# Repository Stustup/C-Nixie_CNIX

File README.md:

# CNIX - Nixie Tube Clock

CNIX is a nixie tube clock that can accept many diffrent nixie tubes with only slight modifications to the tube carrier board. 

The motivation was that there are not many clocks out there that let you use almost any nixie tube you like. Most have fixed power supplies, 
underdesigned driver stages or inflexible microcontrollers. I hope to tackle these problems with an adjustable boost converter PSU, extremely 
flexible (and electrically protected) driver stages and an open source firmware written with free tools.

## **Schematic**

The control board consists of 3 parts:
- Power Supply
- Microcontroller
- I/O
- GPIO header

Power comes from a simple USB-C plug configured for 5V 3A max with the 5k1 CC line resistors. I thought about adding a PD controller for higher input voltages, but this would just have added complexity and locked you into more expensive USB PD power supplies.

The µC is a STM32G051, because it has an included RTC *with* added Vbat pin for an external battery, so that the RTC remembers time even when powered off. 
The unused GPIOs are broken out to a connector, so that in the future one could add cool stuff like a radio time reciever, a display or wifi.
Time is set manually with the push buttons on top. 

The PSU is heavily inspired by [this site](https://surfncircuits.com/2018/02/03/optimizing-the-5v-to-170v-nixie-tube-power-supply-design-part-2/). I highly advise you giving it a read. The article goes in depth with boost converter design and its challanges.

The ht power supply is a DCM boost converter powered by the UCC3803. An active low enable pin is realized via pulling the frequency RC combination low. With normal usage temperature of around 50-60°C are reached by the output transistor and the controller, which is a safe area. The case is designed so that a convection current of air is directed over the power supply at all times. This vent should not be blocked.  

The driver consists of 4 CD4028 BCD to Decimal converters and 6 SN75468 high voltage drivers. The SN75468 only work up top 100V, but when using two 48V zener diodes as clamps, the voltage on the torned off digits never reach above 100V and above the startup voltage of the nixies. So win win.

I didn't use the old high voltage nixie driving shift registers as they are more and more hard to find for a reasonable price. Also i did not use shift registers at all, to simplify programming and wiring. Instead the whole Port B of the STM32 is used as a big 16 bit control register where the numbers are encoded in BCD. This ensures that there can not be 2 turned on digits at the same time in one tube to prevent bugs and damaging the beautiful nixies. 
Except the decoupling capacitors, diopdes and LEDS, everything is a simple to reflow solder IC, The tube pins have to be assembled manually (by putting them on a tube an inserting it into the holes before soldering it to ensure perfect alignment).  

The case is designed in FreeCAD and printed in PLA or PETG. Assembly is a bit of a hassle, but the fit is perfect. You can print a front plate, but i think the clock is vastly more beautiful when paired with a wooden front plate. Drill files for this are within the CAD folder. The holes for the LED front indicators can be filled with a 3mm lightpipe cut to length, to get a beautiful finish. 
Case, PCB and front plate are screwed together with 15mm M3 wood screws.

## **Neat features**

### <u>Adaptability</u>
If you want to use any other nixie (up to around 5mA per tube of HT supply current) just modify the tube board PCB to fit your tubes. The driver, power supply and control logic should all be compatible with any other tube. Of course you have to modify the driving circuit when not using the simple common anode topology.

### <u>USB-C support</u>
Use any USB power supply with a minimum current of 1.7A (The startup of the boost converter needs a lot of current) Standard power consumption is around 2W (400mA at 5V) when the boost converter is powered on and around 0.2W (40mA at 5V) when the boost converter is powered down. 

### <u>Fallback structure</u>
If for some reason you change your mind while setting the start/stop times or the main time, just wait for around a minute. The menu will exit automatically, discard all changes and get back to the main time display.

### <u>Date and Sensor display</u>
Press the "plus" or "minus" buttons to cycle through submenus in this order: 
Main Time display -> Date display -> Sensor Display
These have a short timeout time to get back to the main Time menu. The sensor display gets disabled when there is no sensor addon board present.

### <u>Automatic daylight saving time (DST)</u>
The clock will calculate DST on its own and set the time correspondingly, even when the DCF77 module is not used.

### <u>Turn on/off timers</u>
You can set power on and off times in the clock natively, so that the nixies dont always glow. With this the HT-power supply also gets deactivated to save power and lifespan of the parts. 
There are two sets of start and stop times set by the buttons on the menu with the lower LED blinking.
The order is: Start1 -> Stop1 -> Start2 -> Stop2.
If all are set to 0, the start stop automatic gets disabled.
The start stop times are saved to a backup register of the µC, so the clock remembers them even when powered off as long as the RTC battery is present. 

#### Peek
When out of the "on" timeframes you can "peek" at the current time for 10s with a press of the menu-button. During these 10s you can jump to all the diffrent menus.

### <u>Addon Boards</u>
The breakout pins next to the µC can be used for addon boards. Pins D2 and D3 of the µC are used to detect those with an ID system. 
| ID    | Board                                 |
|-------|---------------------------------------|
| 0b11  | No Addon board installed -> defualt   |
| 0b00  | DCF77 Addon Board used                |
| 0b01  | not yet used                          |
| 0b10  | not yet used                          |

Most of the hardware features of the STM32G051 should be mapped to the pins on the breakout. If not you're out of luck (it's open source, so just change it). Stuff like the ST-Link programming pins or I2C are broken out on extra headers to simplify future expansion.

#### DCF77 Addon Board

In germany (and most of europe) we have the DCF77 signal pushed out by the radio transmitter near Frankfurt. 
This board hosts a cheap module from ebay and a HTU21D temperature and humidity sensor. The driver is already programmed into the Control Board and gets enabled when this addon board is detected. 
When a valid time is recieved the manual timeSet menu gets disabled, to prevent fuckery.
It is setup, that every night at 2 an alarm gets triggered by the RTC to recalibrate time. If the  time-parity bit is not matched within a 20 minute timeout an attempt counter is incremented, which gets saved to a backup-register inside the RTC. As long as a RTC battery is powering the µC this register is kept even when the power is off. 
If the attempt counter reches 3 days without successful calibration against the radio time the manual timeSet menu gets enabled again.

On the DCF77 Addon board there is a single pin to give structural strength to a simple perfboard on the main breakout bus. One can use this in tandem with the A1, A2, A3, A4, F0 and F1 pins.

Ideas for future addon Boards: 
- ESP32 addon board to integrate WiFi time synchronisation or HomeAssistant integration
- Other sensors like air quality sensors
- maybe displays?

## TODO

- Change to new MCU. STM32H5 for USBC pd -> more efficient boost converter because higher input voltage
- Sleep modes during off times paired with wakeup alarms at start times -> reduce power consumption even more
- Improve the case to simplify assembly
- More tube boards to fit more types of nixies (IN-14 e.G.)
- BOM optimization to reduce number of unique parts
- galvanic isolation between high voltage areas and µC GPIOs

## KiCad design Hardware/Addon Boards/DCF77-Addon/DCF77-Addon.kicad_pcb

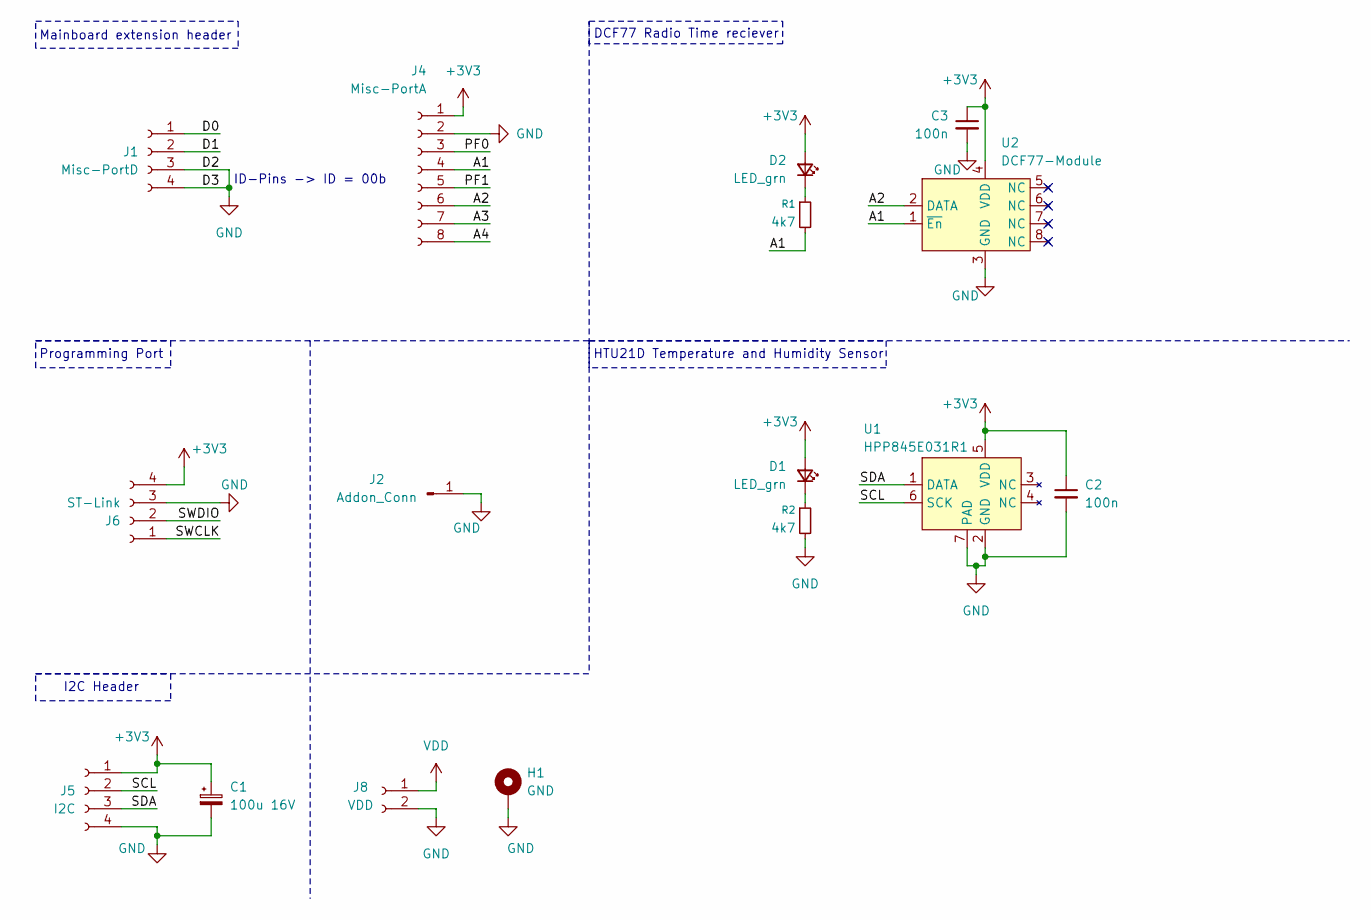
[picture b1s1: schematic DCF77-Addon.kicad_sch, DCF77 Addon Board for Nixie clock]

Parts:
C1: 100u 16V; CP_Elec_6.3x7.7
C2, C3: 100n; C_0805_2012Metric_Pad1.18x1.45mm_HandSolder
D1, D2: LED_grn; LED_0805_2012Metric_Pad1.15x1.40mm_HandSolder
H1: GND; TestPoint_Loop_D3.80mm_Drill2.0mm
J1: Misc-PortD; PinSocket_1x04_P2.54mm_Vertical
J2: Addon_Conn; PinHeader_1x01_P2.54mm_Vertical
J4: Misc-PortA; PinSocket_1x08_P2.54mm_Vertical
J5: I2C; PinSocket_1x04_P2.54mm_Vertical
J6: ST-Link; PinSocket_1x04_P2.54mm_Vertical
J8: VDD; PinSocket_1x02_P2.54mm_Vertical
R1, R2: 4k7; R_0805_2012Metric_Pad1.20x1.40mm_HandSolder
U1: HPP845E031R1; Maxim_TDFN-6-1EP_3x3mm_P0.95mm_EP1.5x2.3mm; Mouser Nr. 824-HPP845E031R1
U2: DCF77-Module

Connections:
+3V3: C1.1, C2.1, C3.1, D1.2 (A), D2.2 (A), J4.1, J5.1, J6.4, U1.5 (VDD), U2.4 (VDD)
/A1: J4.4, R1.2, U2.1 (~En)
/A2: J4.6, U2.2 (DATA)
/A3: J4.7
/A4: J4.8
/D0: J1.1
/D1: J1.2
/PF0: J4.3
/PF1: J4.5
/SCL: J5.2, U1.6 (SCK)
/SDA: J5.3, U1.1 (DATA)
/SWCLK: J6.1
/SWDIO: J6.2
GND: C1.2, C2.2, C3.2, H1.1 (1_1), J1.3, J1.4, J2.1 (Pin_1_1), J4.2, J5.4, J6.3, J8.2, R2.2, U1.2 (GND), U1.7 (PAD), U2.3 (GND)
unnamed: D1.1 (K), R2.1
unnamed: D2.1 (K), R1.1
VDD: J8.1

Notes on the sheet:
HTU21D Temperature and Humidity Sensor
DCF77 Radio Time reciever
Programming Port
ID-Pins -> ID = 00b
Mainboard extension header
I2C Header

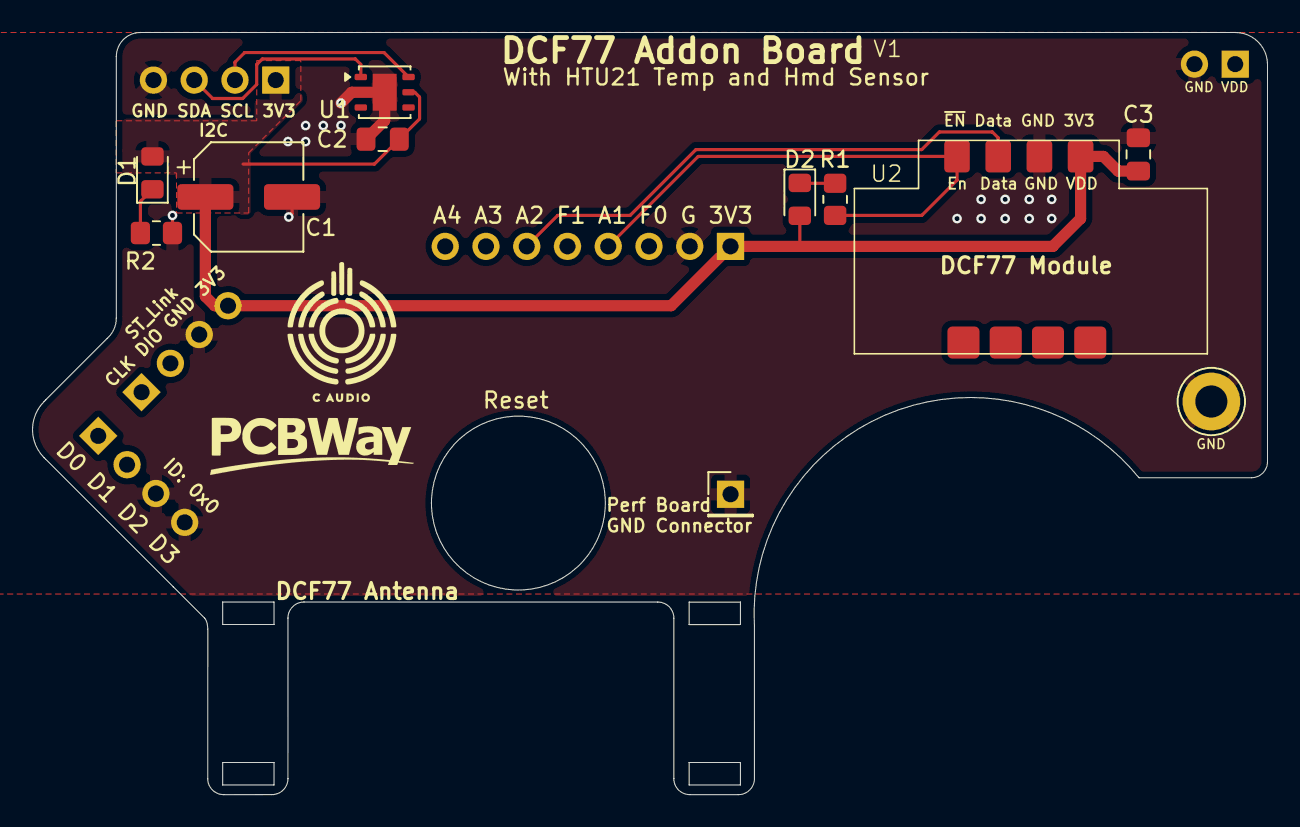
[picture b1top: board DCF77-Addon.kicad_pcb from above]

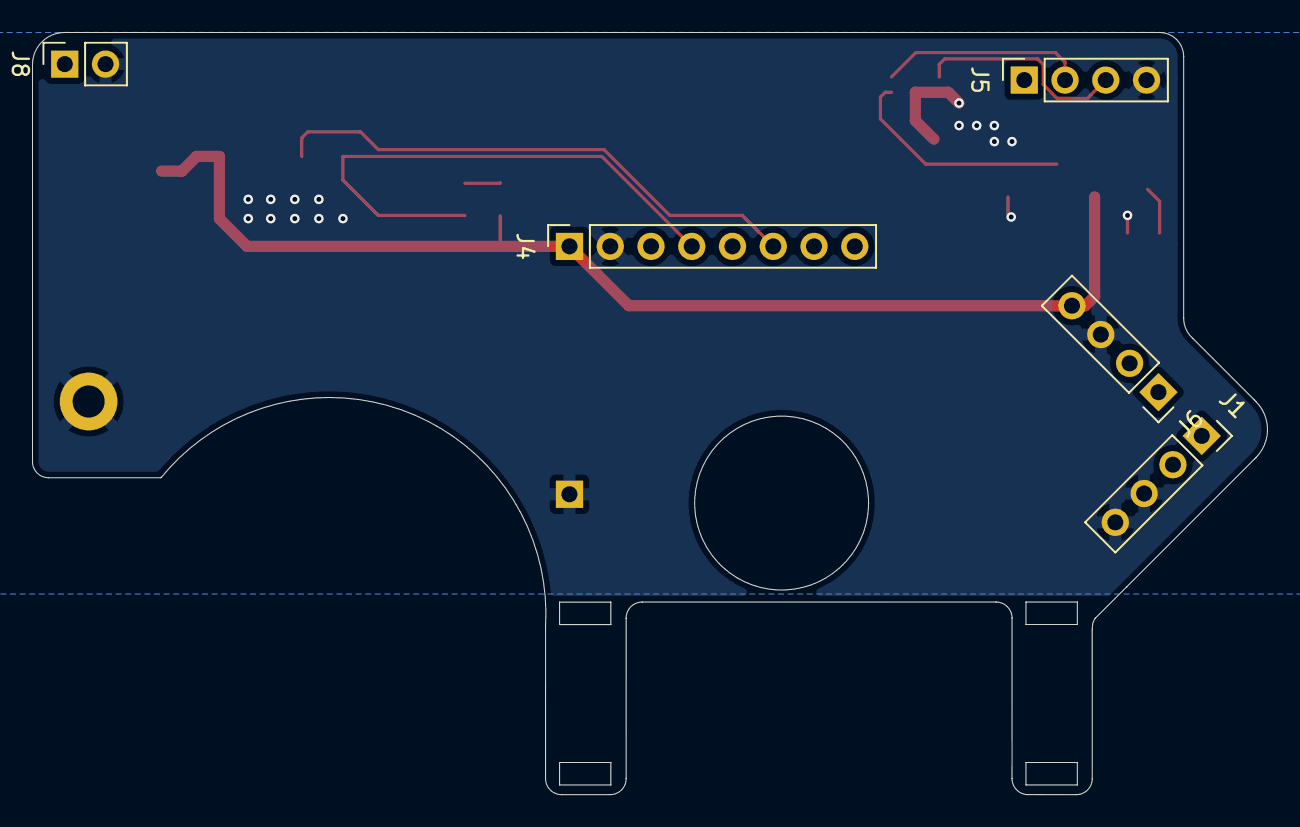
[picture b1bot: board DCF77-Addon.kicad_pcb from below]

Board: 2 copper layers, 77.0 x 47.5 mm, 16 parts (5 on the bottom side), 8 nets.

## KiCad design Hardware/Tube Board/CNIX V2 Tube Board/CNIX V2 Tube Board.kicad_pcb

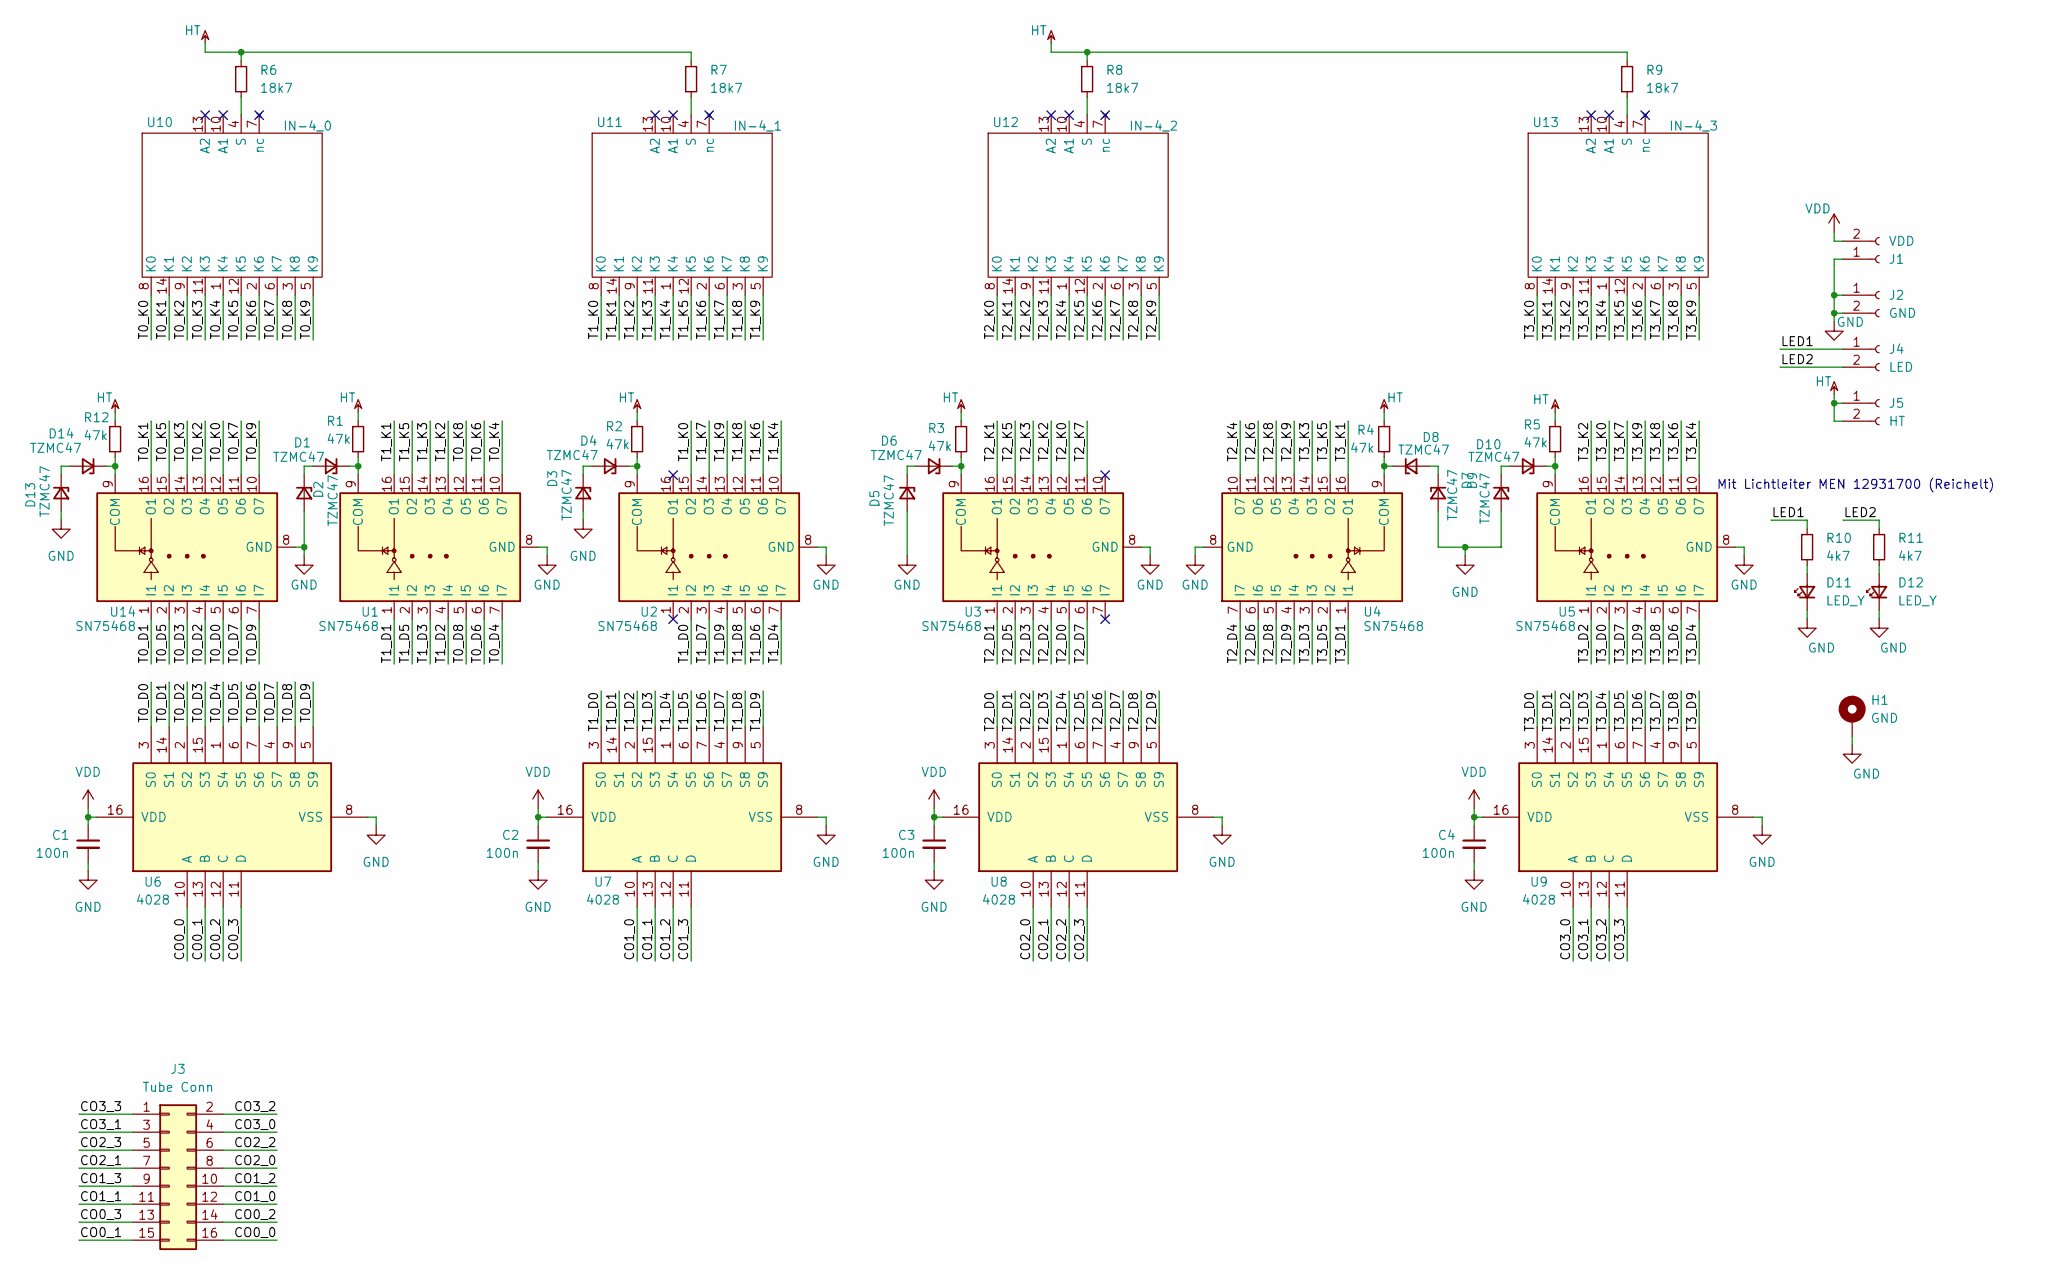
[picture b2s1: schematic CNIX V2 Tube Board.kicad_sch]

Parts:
C1, C2, C3, C4: 100n; C_0805_2012Metric_Pad1.18x1.45mm_HandSolder
D1, D2, D3, D4, D5, D6, D7, D8, D9, D10, D13, D14: TZMC47; D_MiniMELF; Mouser URL 78-TZMC47
D11, D12: LED_Y; LED_0805_2012Metric_Pad1.15x1.40mm_HandSolder
H1: GND; TestPoint_Plated_Hole_D3.0mm
J1: VDD; PinHeader_1x02_P2.54mm_Vertical
J2: GND; PinHeader_1x02_P2.54mm_Vertical
J3: Tube Conn; PinHeader_2x08_P2.54mm_Vertical
J4: LED; PinHeader_1x02_P2.54mm_Vertical
J5: HT; PinHeader_1x02_P2.54mm_Vertical
R1, R2, R3, R4, R5, R12: 47k; R_0805_2012Metric; Mouser Nr. 603-AC0805FR-1347KL
R6, R7, R8, R9: 18k7; R_1206_3216Metric_Pad1.30x1.75mm_HandSolder; Mouser Nr. 603-RC1206FR-0718K7L
R10, R11: 4k7; R_0805_2012Metric_Pad1.20x1.40mm_HandSolder; Mouser Nr. 603-RC0805FR-074K7P
U1, U2, U3, U4, U5, U14: SN75468; SOIC-16_3.9x9.9mm_P1.27mm; Mouser Nr. 595-SN75468DR
U6, U7, U8, U9: 4028; SOIC-16_3.9x9.9mm_P1.27mm; Mouser Nr. 595-CD4028BM96
U10: IN-4_0; IN-4
U11: IN-4_1; IN-4
U12: IN-4_2; IN-4
U13: IN-4_3; IN-4

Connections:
/CO0_0: J3.16, U6.10 (A)
/CO0_1: J3.15, U6.13 (B)
/CO0_2: J3.14, U6.12 (C)
/CO0_3: J3.13, U6.11 (D)
/CO1_0: J3.12, U7.10 (A)
/CO1_1: J3.11, U7.13 (B)
/CO1_2: J3.10, U7.12 (C)
/CO1_3: J3.9, U7.11 (D)
/CO2_0: J3.8, U8.10 (A)
/CO2_1: J3.7, U8.13 (B)
/CO2_2: J3.6, U8.12 (C)
/CO2_3: J3.5, U8.11 (D)
/CO3_0: J3.4, U9.10 (A)
/CO3_1: J3.3, U9.13 (B)
/CO3_2: J3.2, U9.12 (C)
/CO3_3: J3.1, U9.11 (D)
/LED1: J4.1, R10.1
/LED2: J4.2, R11.1
/T0_D0: U6.3 (S0), U14.5 (I5)
/T0_D1: U6.14 (S1), U14.1 (I1)
/T0_D2: U6.2 (S2), U14.4 (I4)
/T0_D3: U6.15 (S3), U14.3 (I3)
/T0_D4: U1.7 (I7), U6.1 (S4)
/T0_D5: U6.6 (S5), U14.2 (I2)
/T0_D6: U1.6 (I6), U6.7 (S6)
/T0_D7: U6.4 (S7), U14.6 (I6)
/T0_D8: U1.5 (I5), U6.9 (S8)
/T0_D9: U6.5 (S9), U14.7 (I7)
/T0_K0: U10.8 (K0), U14.12 (O5)
/T0_K1: U10.14 (K1), U14.16 (O1)
/T0_K2: U10.9 (K2), U14.13 (O4)
/T0_K3: U10.11 (K3), U14.14 (O3)
/T0_K4: U1.10 (O7), U10.1 (K4)
/T0_K5: U10.12 (K5), U14.15 (O2)
/T0_K6: U1.11 (O6), U10.2 (K6)
/T0_K7: U10.6 (K7), U14.11 (O6)
/T0_K8: U1.12 (O5), U10.3 (K8)
/T0_K9: U10.5 (K9), U14.10 (O7)
/T1_D0: U2.2 (I2), U7.3 (S0)
/T1_D1: U1.1 (I1), U7.14 (S1)
/T1_D2: U1.4 (I4), U7.2 (S2)
/T1_D3: U1.3 (I3), U7.15 (S3)
/T1_D4: U2.7 (I7), U7.1 (S4)
/T1_D5: U1.2 (I2), U7.6 (S5)
/T1_D6: U2.6 (I6), U7.7 (S6)
/T1_D7: U2.3 (I3), U7.4 (S7)
/T1_D8: U2.5 (I5), U7.9 (S8)
/T1_D9: U2.4 (I4), U7.5 (S9)
/T1_K0: U2.15 (O2), U11.8 (K0)
/T1_K1: U1.16 (O1), U11.14 (K1)
/T1_K2: U1.13 (O4), U11.9 (K2)
/T1_K3: U1.14 (O3), U11.11 (K3)
/T1_K4: U2.10 (O7), U11.1 (K4)
/T1_K5: U1.15 (O2), U11.12 (K5)
/T1_K6: U2.11 (O6), U11.2 (K6)
/T1_K7: U2.14 (O3), U11.6 (K7)
/T1_K8: U2.12 (O5), U11.3 (K8)
/T1_K9: U2.13 (O4), U11.5 (K9)
/T2_D0: U3.5 (I5), U8.3 (S0)
/T2_D1: U3.1 (I1), U8.14 (S1)
/T2_D2: U3.4 (I4), U8.2 (S2)
/T2_D3: U3.3 (I3), U8.15 (S3)
/T2_D4: U4.7 (I7), U8.1 (S4)
/T2_D5: U3.2 (I2), U8.6 (S5)
/T2_D6: U4.6 (I6), U8.7 (S6)
/T2_D7: U3.6 (I6), U8.4 (S7)
/T2_D8: U4.5 (I5), U8.9 (S8)
/T2_D9: U4.4 (I4), U8.5 (S9)
/T2_K0: U3.12 (O5), U12.8 (K0)
/T2_K1: U3.16 (O1), U12.14 (K1)
/T2_K2: U3.13 (O4), U12.9 (K2)
/T2_K3: U3.14 (O3), U12.11 (K3)
/T2_K4: U4.10 (O7), U12.1 (K4)
/T2_K5: U3.15 (O2), U12.12 (K5)
/T2_K6: U4.11 (O6), U12.2 (K6)
/T2_K7: U3.11 (O6), U12.6 (K7)
/T2_K8: U4.12 (O5), U12.3 (K8)
/T2_K9: U4.13 (O4), U12.5 (K9)
/T3_D0: U5.2 (I2), U9.3 (S0)
/T3_D1: U4.1 (I1), U9.14 (S1)
/T3_D2: U5.1 (I1), U9.2 (S2)
/T3_D3: U4.3 (I3), U9.15 (S3)
/T3_D4: U5.7 (I7), U9.1 (S4)
/T3_D5: U4.2 (I2), U9.6 (S5)
/T3_D6: U5.6 (I6), U9.7 (S6)
/T3_D7: U5.3 (I3), U9.4 (S7)
/T3_D8: U5.5 (I5), U9.9 (S8)
/T3_D9: U5.4 (I4), U9.5 (S9)
/T3_K0: U5.15 (O2), U13.8 (K0)
/T3_K1: U4.16 (O1), U13.14 (K1)
/T3_K2: U5.16 (O1), U13.9 (K2)
/T3_K3: U4.14 (O3), U13.11 (K3)
/T3_K4: U5.10 (O7), U13.1 (K4)
/T3_K5: U4.15 (O2), U13.12 (K5)
/T3_K6: U5.11 (O6), U13.2 (K6)
/T3_K7: U5.14 (O3), U13.6 (K7)
/T3_K8: U5.12 (O5), U13.3 (K8)
/T3_K9: U5.13 (O4), U13.5 (K9)
GND: C1.2, C2.2, C3.2, C4.2, D2.2 (A), D3.2 (A), D5.2 (A), D7.2 (A), D9.2 (A), D11.1 (K), D12.1 (K), D13.2 (A), H1.1, J1.1, J2.1, J2.2, U1.8 (GND), U2.8 (GND), U3.8 (GND), U4.8 (GND), U5.8 (GND), U6.8 (VSS), U7.8 (VSS), U8.8 (VSS), U9.8 (VSS), U14.8 (GND)
HT: J5.1, J5.2, R1.1, R2.1, R3.1, R4.1, R5.1, R6.1, R7.1, R8.1, R9.1, R12.1
unnamed: D1.2 (A), D2.1 (K)
unnamed: D1.1 (K), R1.2, U1.9 (COM)
unnamed: D3.1 (K), D4.2 (A)
unnamed: D4.1 (K), R2.2, U2.9 (COM)
unnamed: D5.1 (K), D6.2 (A)
unnamed: D6.1 (K), R3.2, U3.9 (COM)
unnamed: D7.1 (K), D8.2 (A)
unnamed: D8.1 (K), R4.2, U4.9 (COM)
unnamed: D9.1 (K), D10.2 (A)
unnamed: D10.1 (K), R5.2, U5.9 (COM)
unnamed: D11.2 (A), R10.2
unnamed: D12.2 (A), R11.2
unnamed: D13.1 (K), D14.2 (A)
unnamed: D14.1 (K), R12.2, U14.9 (COM)
unnamed: R6.2, U10.4 (S)
unnamed: R7.2, U11.4 (S)
unnamed: R8.2, U12.4 (S)
unnamed: R9.2, U13.4 (S)
VDD: C1.1, C2.1, C3.1, C4.1, J1.2, U6.16 (VDD), U7.16 (VDD), U8.16 (VDD), U9.16 (VDD)

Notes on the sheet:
Mit Lichtleiter MEN 12931700 (Reichelt)

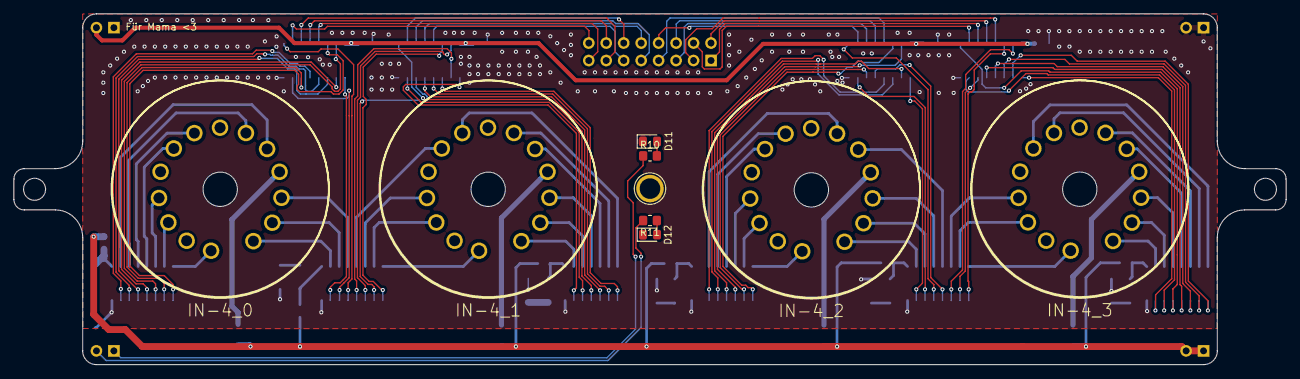
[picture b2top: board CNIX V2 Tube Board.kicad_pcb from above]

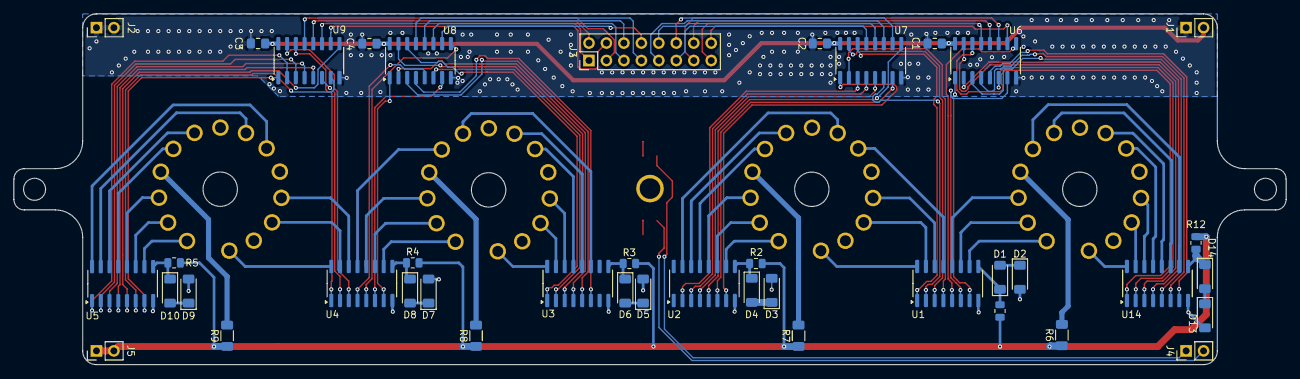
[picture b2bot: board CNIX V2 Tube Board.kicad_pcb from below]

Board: 2 copper layers, 185.0 x 51.0 mm, 50 parts (41 on the bottom side), 119 nets.

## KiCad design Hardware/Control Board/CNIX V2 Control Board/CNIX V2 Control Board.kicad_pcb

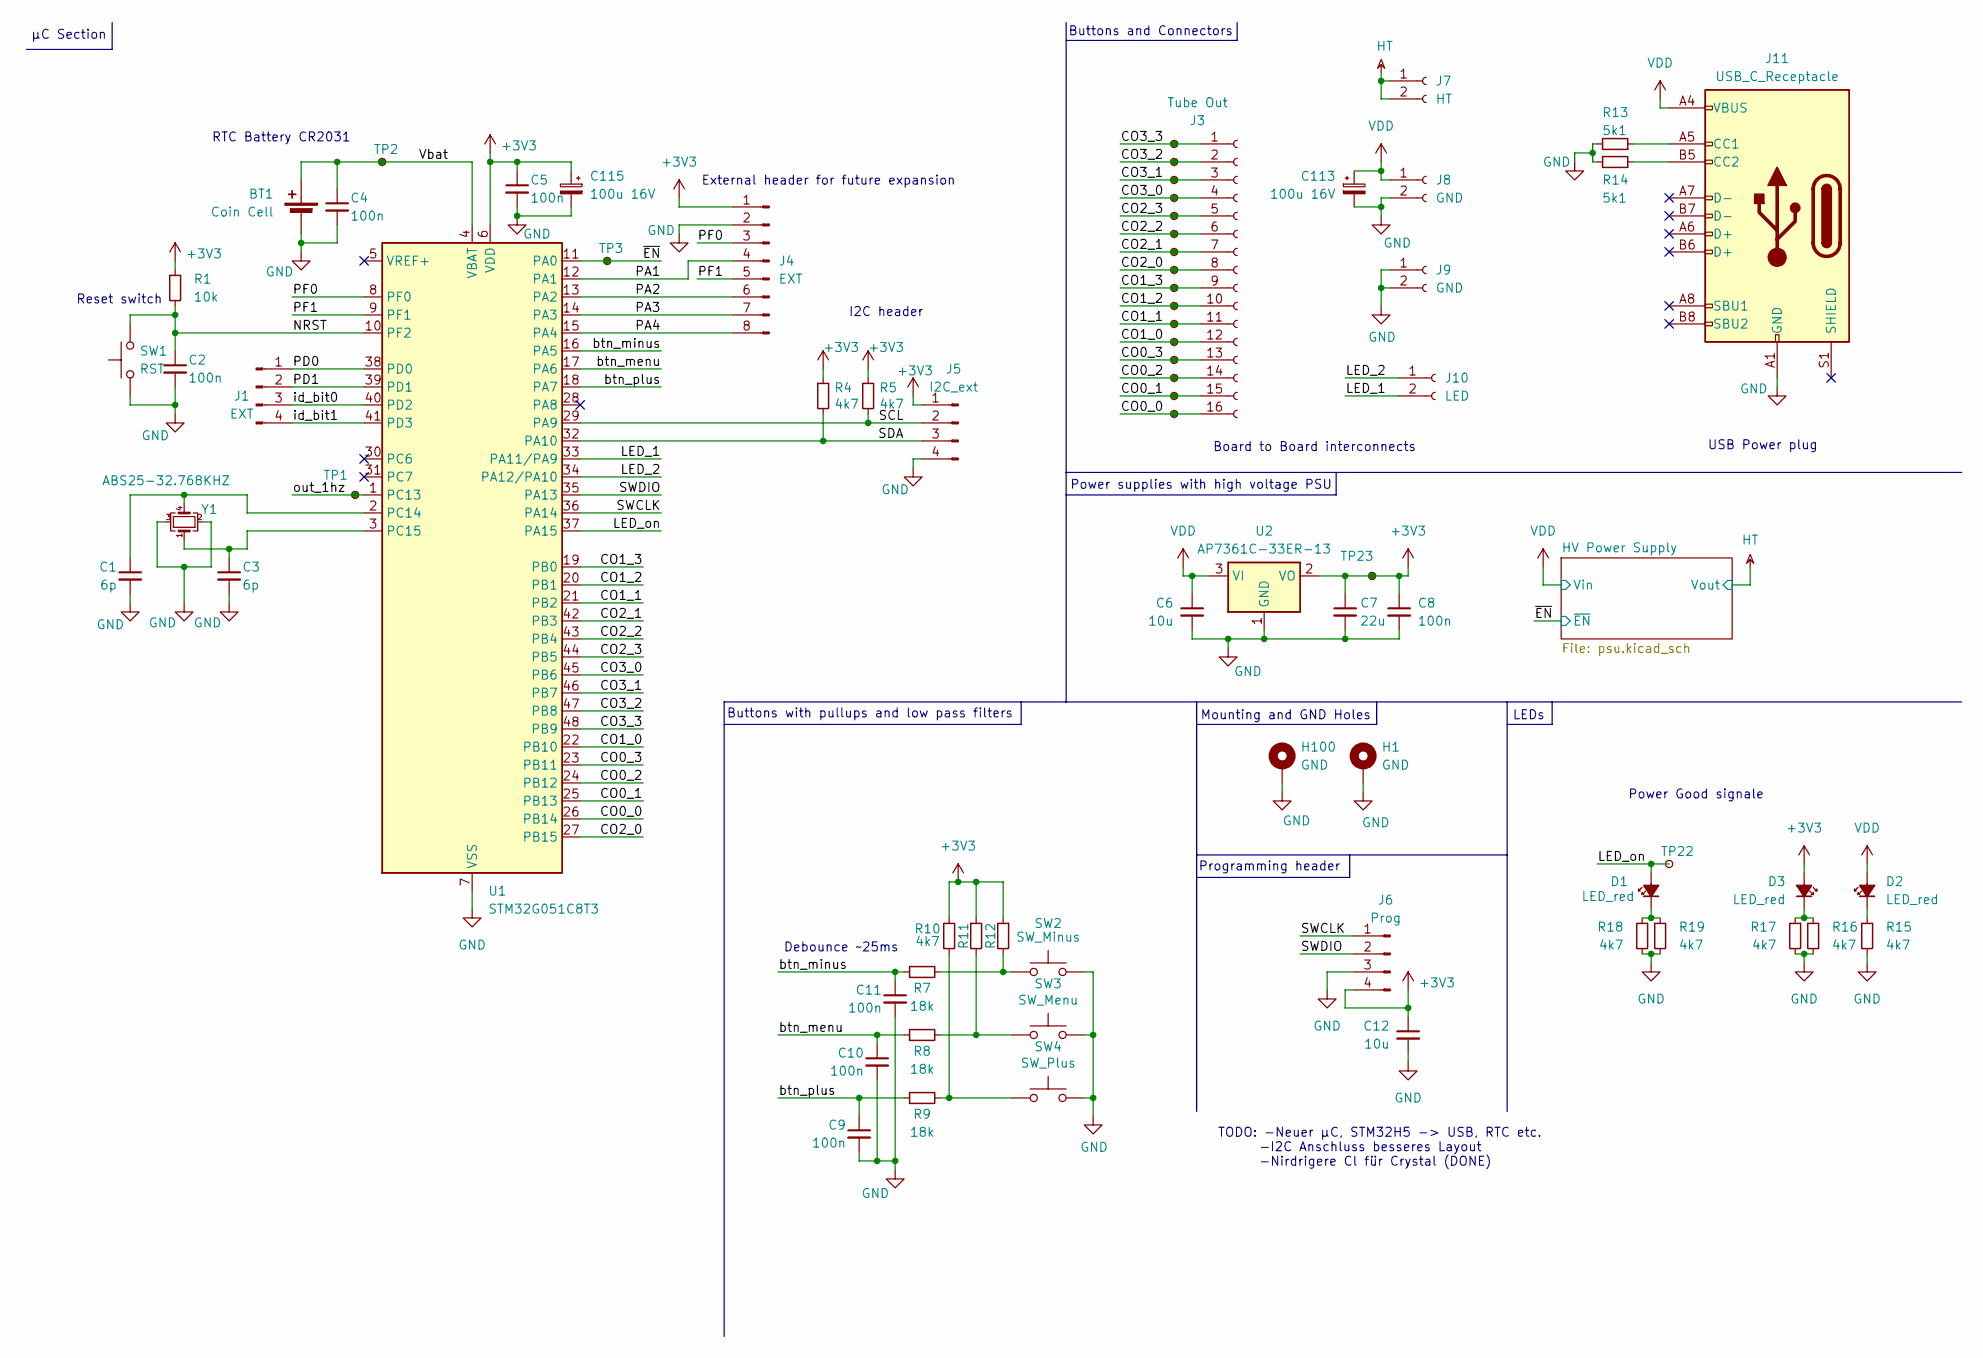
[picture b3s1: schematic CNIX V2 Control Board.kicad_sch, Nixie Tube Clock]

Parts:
BT1: Coin Cell; BatteryHolder_Renata_SMTU2032-LF_1x2032; Mouser Nr. 614-SMTU2032-LF.TR
C1, C3: 6p; C_0805_2012Metric_Pad1.18x1.45mm_HandSolder; Mouser Nr. 80-C0805C180K5HACTU
C2, C4, C5, C8, C9, C10, C11: 100n; C_0805_2012Metric_Pad1.18x1.45mm_HandSolder
C6, C12: 10u; C_0805_2012Metric_Pad1.18x1.45mm_HandSolder; Mouser Nr. 187-CL21B106KPQNNNE
C7: 22u; C_0805_2012Metric_Pad1.18x1.45mm_HandSolder; Mouser Nr. 187-CL21A226MQQNNNG
C113, C115: 100u 16V; CP_Elec_6.3x7.7; Mouser Nr. 710-865080343009
D1, D2, D3: LED_red; LED_0805_2012Metric_Pad1.15x1.40mm_HandSolder
H1: GND; TestPoint_Loop_D3.80mm_Drill2.0mm
H100: GND; TestPoint_Plated_Hole_D3.0mm
J1: EXT; PinHeader_1x04_P2.54mm_Vertical
J3: Tube Out; PinSocket_2x08_P2.54mm_Vertical
J4: EXT; PinHeader_1x08_P2.54mm_Vertical
J5: I2C_ext; PinHeader_1x04_P2.54mm_Vertical
J6: Prog; PinHeader_1x04_P2.54mm_Vertical
J7: HT; PinSocket_1x02_P2.54mm_Vertical
J8, J9: GND; PinSocket_1x02_P2.54mm_Vertical
J10: LED; PinSocket_1x02_P2.54mm_Vertical
J11: USB_C_Receptacle; USB_C_Receptacle_GCT_USB4085
R1: 10k; R_0805_2012Metric_Pad1.20x1.40mm_HandSolder
R4, R5, R10, R11, R12, R15, R16, R17, R18, R19: 4k7; R_0805_2012Metric_Pad1.20x1.40mm_HandSolder; Mouser Nr. 603-RC0805FR-074K7P
R7, R8, R9: 18k; R_0805_2012Metric_Pad1.20x1.40mm_HandSolder; Mouser Nr. 603-RC0805FR-074K7P
R13, R14: 5k1; R_0805_2012Metric_Pad1.20x1.40mm_HandSolder; Mouser Nr. 652-CR0805FX-5101ELF
SW1: RST; SW_SPST_Omron_B3FS-100xP
SW2: SW_Minus; SW_Tactile_SPST_Angled_PTS645Vx31-2LFS
SW3: SW_Menu; SW_Tactile_SPST_Angled_PTS645Vx31-2LFS
SW4: SW_Plus; SW_Tactile_SPST_Angled_PTS645Vx31-2LFS
TP1, TP2, TP3, TP22, TP23: TestPoint_Small; TestPoint_Pad_D1.5mm
TP4, TP5, TP6, TP7, TP8, TP9, TP10, TP11, TP12, TP13, TP14, TP15, TP16, TP17, TP18, TP19: TestPoint_Small; TestPoint_THTPad_D1.0mm_Drill0.5mm
U1: STM32G051C8T3; LQFP-48_7x7mm_P0.5mm; Mouser Nr. 511-STM32G051C8T3
U2: AP7361C-33ER-13; SOT-223-3_TabPin2; Mouser-Nr. 621-AP7361C-33ER-13
Y1: ABS25-32.768KHZ; Crystal_SMD_Abracon_ABS25-4Pin_8.0x3.8mm; Mouser Nr. 815-ABS25-32.7-6-1-T

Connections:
+3V3: C5.1, C7.1, C8.1, C12.1, C115.1, D3.2 (A), J4.1, J5.1, J6.4, R1.1, R4.1, R5.1, R10.2, R11.1, R12.1, TP23.1, U1.6 (VDD), U2.2 (VO)
/CO0_0: J3.16, TP19.1, U1.26 (PB14)
/CO0_1: J3.15, TP18.1, U1.25 (PB13)
/CO0_2: J3.14, TP17.1, U1.24 (PB12)
/CO0_3: J3.13, TP16.1, U1.23 (PB11)
/CO1_0: J3.12, TP15.1, U1.22 (PB10)
/CO1_1: J3.11, TP14.1, U1.21 (PB2)
/CO1_2: J3.10, TP13.1, U1.20 (PB1)
/CO1_3: J3.9, TP12.1, U1.19 (PB0)
/CO2_0: J3.8, TP11.1, U1.27 (PB15)
/CO2_1: J3.7, TP10.1, U1.42 (PB3)
/CO2_2: J3.6, TP9.1, U1.43 (PB4)
/CO2_3: J3.5, TP8.1, U1.44 (PB5)
/CO3_0: J3.4, TP7.1, U1.45 (PB6)
/CO3_1: J3.3, TP6.1, U1.46 (PB7)
/CO3_2: J3.2, TP5.1, U1.47 (PB8)
/CO3_3: J3.1, TP4.1, U1.48 (PB9)
/LED_1: J10.2, U1.33 (PA11/PA9)
/LED_2: J10.1, U1.34 (PA12/PA10)
/LED_on: D1.2 (A), TP22.1, U1.37 (PA15)
/NRST: C2.1, R1.2, SW1.2, U1.10 (PF2)
/PA1: J4.4, U1.12 (PA1)
/PA2: J4.6, U1.13 (PA2)
/PA3: J4.7, U1.14 (PA3)
/PA4: J4.8, U1.15 (PA4)
/PD0: J1.1, U1.38 (PD0)
/PD1: J1.2, U1.39 (PD1)
/PF0: J4.3, U1.8 (PF0)
/PF1: J4.5, U1.9 (PF1)
/SCL: J5.2, R5.2, U1.29 (PA9)
/SDA: J5.3, R4.2, U1.32 (PA10)
/SWCLK: J6.1, U1.36 (PA14)
/SWDIO: J6.2, U1.35 (PA13)
/Vbat: BT1.1 (+), C4.1, TP2.1, U1.4 (VBAT)
/btn_menu: C10.1, R8.1, U1.17 (PA6)
/btn_minus: C11.1, R7.1, U1.16 (PA5)
/btn_plus: C9.1, R9.1, U1.18 (PA7)
/id_bit0: J1.3, U1.40 (PD2)
/id_bit1: J1.4, U1.41 (PD3)
/out_1hz: TP1.1, U1.1 (PC13)
/~EN: TP3.1, U1.11 (PA0); also elsewhere on the board
GND: BT1.2 (-), C1.2, C2.2, C3.2, C4.2, C5.2, C6.2, C7.2, C8.2, C9.2, C10.2, C11.2, C12.2, C113.2, C115.2, H1.1, H100.1, J4.2, J5.4, J6.3, J8.2, J9.1, J9.2, J11.A1 (GND), J11.A12 (GND), J11.B1 (GND), J11.B12 (GND), R13.2, R14.2, R15.2, R16.2, R17.2, R18.2, R19.2, SW1.1, SW2.2, SW3.2, SW4.2, U1.7 (VSS), U2.1 (GND), Y1.2, Y1.3; also elsewhere on the board
HT: J7.1, J7.2; also elsewhere on the board
unnamed 52: D1.1 (K), R18.1, R19.1; also elsewhere on the board
unnamed: D2.1 (K), R15.1
unnamed: D3.1 (K), R16.1, R17.1
unnamed: J11.A5 (CC1), R13.1
unnamed: J11.B5 (CC2), R14.1
unnamed: R9.2, R10.1, SW4.1
unnamed: R8.2, R11.2, SW3.1
unnamed: R7.2, R12.2, SW2.1
unnamed: C1.1, U1.2 (PC14), Y1.4
unnamed: C3.1, U1.3 (PC15), Y1.1
VDD: C6.1, C113.1, D2.2 (A), J8.1, J11.A4 (VBUS), J11.A9 (VBUS), J11.B4 (VBUS), J11.B9 (VBUS), U2.3 (VI); also elsewhere on the board

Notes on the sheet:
Board to Board interconnects
RTC Battery CR2031
µC Section
Programming header
External header for future expansion
Mounting and GND Holes
TODO: -Neuer µC, STM32H5 -> USB, RTC etc. -I2C Anschluss besseres Layout -Nirdrigere Cl für Crystal (DONE)
Power supplies with high voltage PSU
Buttons with pullups and low pass filters
Power Good signale
I2C header
USB Power plug
Debounce ~25ms
Reset switch
LEDs
Buttons and Connectors

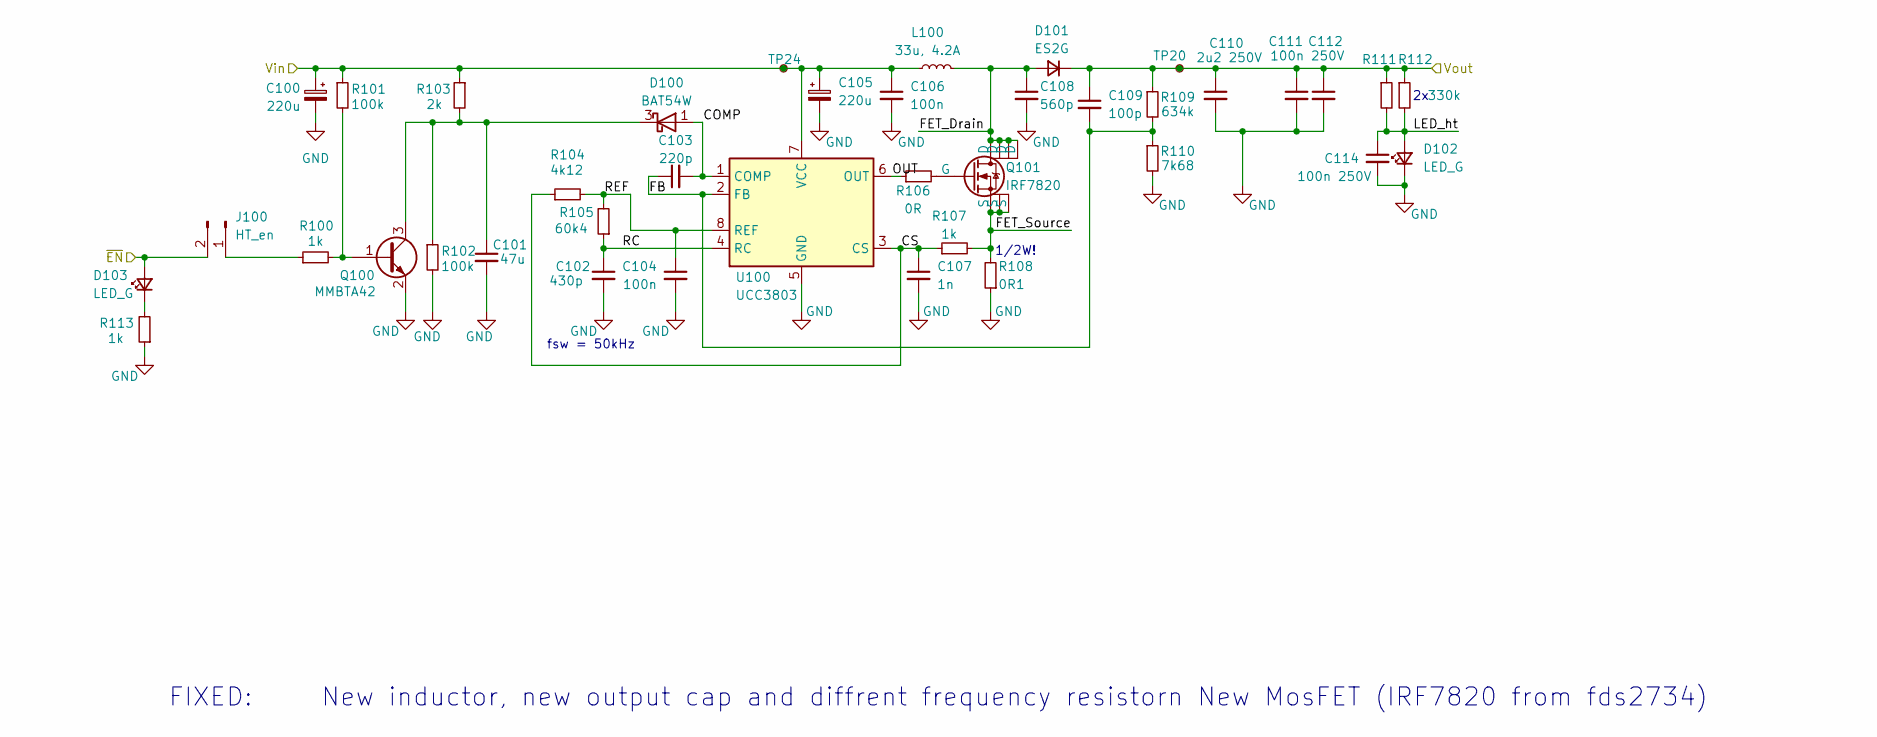
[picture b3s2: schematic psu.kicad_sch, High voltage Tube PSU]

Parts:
C100, C105: 220u; CP_Elec_8x10; Mouser Nr. 647-UUX1E221MNL6GS
C101: 47u; C_0805_2012Metric_Pad1.18x1.45mm_HandSolder; Mouser Nr. 187-CL21A476MRYNNNE
C102: 430p; C_0805_2012Metric_Pad1.18x1.45mm_HandSolder; Mouser Nr. 80-C0805C431J5G
C103: 220p; C_0805_2012Metric_Pad1.18x1.45mm_HandSolder; Mouser Nr. 710-885012207082
C104, C106: 100n; C_0805_2012Metric_Pad1.18x1.45mm_HandSolder
C107: 1n; C_0805_2012Metric_Pad1.18x1.45mm_HandSolder; Mouser Nr. 187-CL21B102KBANNNC
C108: 560p; C_0805_2012Metric_Pad1.18x1.45mm_HandSolder; Mouser Nr. 80-C0805C561K2R
C109: 100p; C_0805_2012Metric_Pad1.18x1.45mm_HandSolder; Mouser Nr. 581-08052C101K
C110: 2u2 250V; C_2220_5750Metric_Pad1.97x5.40mm_HandSolder; Mouser Nr. 710-885342214003
C111: 100nf 250V; C_0805_2012Metric_Pad1.18x1.45mm_HandSolder; Mouser Nr. 810-CGA4J3X7T2E104MA
C112, C114: 100n 250V; C_0805_2012Metric_Pad1.18x1.45mm_HandSolder; Mouser Nr. 810-CGA4J3X7T2E104MA
D100: BAT54W; SOT-323_SC-70; Mouser-Nr. 637-BAT54W
D101: ES2G; D_SMB_Handsoldering; Mouser Nr. 603-ES2G
D102, D103: LED_G; LED_0805_2012Metric
J100: HT_en; PinHeader_1x02_P2.54mm_Vertical
L100: 33u, 4.2A; L_12x12mm_H8mm; Mouser Nr. 7447709330
Q100: MMBTA42; SOT-23
Q101: IRF7820; SO-8_3.9x4.9mm_P1.27mm
R100, R107, R113: 1k; R_0805_2012Metric_Pad1.20x1.40mm_HandSolder
R101, R102: 100k; R_0805_2012Metric_Pad1.20x1.40mm_HandSolder
R103: 2k; R_0805_2012Metric_Pad1.20x1.40mm_HandSolder; Mouser Nr. 603-RC0805FR-132KL
R104: 4k12; R_0805_2012Metric_Pad1.20x1.40mm_HandSolder; Mouser Nr. 603-RC0805FR-074K12L
R105: 60k4; R_0805_2012Metric_Pad1.20x1.40mm_HandSolder; Mouser Nr. 603-RE0805FRE0747KL
R106: 0R; R_0805_2012Metric_Pad1.20x1.40mm_HandSolder
R108: 0R1; R_1206_3216Metric_Pad1.30x1.75mm_HandSolder; Mouser Nr. 660-UR73VH2BTTDR100F
R109: 634k; R_1206_3216Metric_Pad1.30x1.75mm_HandSolder; Mouser Nr. 71-CRCW0805634KFKEA
R110: 7k68; R_1206_3216Metric_Pad1.30x1.75mm_HandSolder; Mouser Nr. 603-RC0805FR-077K68L
R111, R112: 330k; R_0805_2012Metric_Pad1.20x1.40mm_HandSolder; Mouser Nr. 603-AC0805FR-07330KL
TP20, TP24: TestPoint_Small; TestPoint_Pad_D1.5mm
U100: UCC3803; SOIC-8_3.9x4.9mm_P1.27mm; Mouser Nr. 595-UCC3803DTR

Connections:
/HV Power Supply/COMP: C103.2, D100.1 (A), U100.1 (COMP)
/HV Power Supply/CS: C107.1, R104.1, R107.1, U100.3 (CS)
/HV Power Supply/FB: C103.1, C109.2, R109.2, R110.1, U100.2 (FB)
/HV Power Supply/FET_Drain: C108.1, D101.2 (A), L100.2, Q101.5 (D), Q101.6 (D), Q101.7 (D), Q101.8 (D)
/HV Power Supply/FET_Source: Q101.1 (S), Q101.2 (S), Q101.3 (S), R107.2, R108.2
/HV Power Supply/LED_ht: C114.1, D102.2 (A), R111.2, R112.2
/HV Power Supply/OUT: R106.1, U100.6 (OUT)
/HV Power Supply/RC: C102.1, R105.1, U100.4 (RC)
/HV Power Supply/REF: C104.1, R104.2, R105.2, U100.8 (REF)
/~EN: D103.2 (A), J100.2; also elsewhere on the board
GND: C100.2, C101.2, C102.2, C104.2, C105.2, C106.2, C107.2, C108.2, C110.2, C111.2, C112.2, C114.2, D102.1 (K), Q100.2 (E), R102.2, R108.1, R110.2, R113.1, U100.5 (GND); also elsewhere on the board
HT: C109.1, C110.1, C111.1, C112.1, D101.1 (K), R109.1, R111.1, R112.1, TP20.1; also elsewhere on the board
unnamed: C101.1, D100.3 (K), Q100.3 (C), R102.1, R103.2
unnamed: D103.1 (K), R113.2
unnamed: J100.1, R100.1
unnamed: Q100.1 (B), R100.2, R101.2
unnamed: Q101.4 (G), R106.2
VDD: C100.1, C105.1, C106.1, L100.1, R101.1, R103.1, TP24.1, U100.7 (VCC); also elsewhere on the board

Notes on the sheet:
FIXED: New inductor, new output cap and diffrent frequency resistorn New MosFET (IRF7820 from fds2734)
fsw = 50kHz
1/2W!
